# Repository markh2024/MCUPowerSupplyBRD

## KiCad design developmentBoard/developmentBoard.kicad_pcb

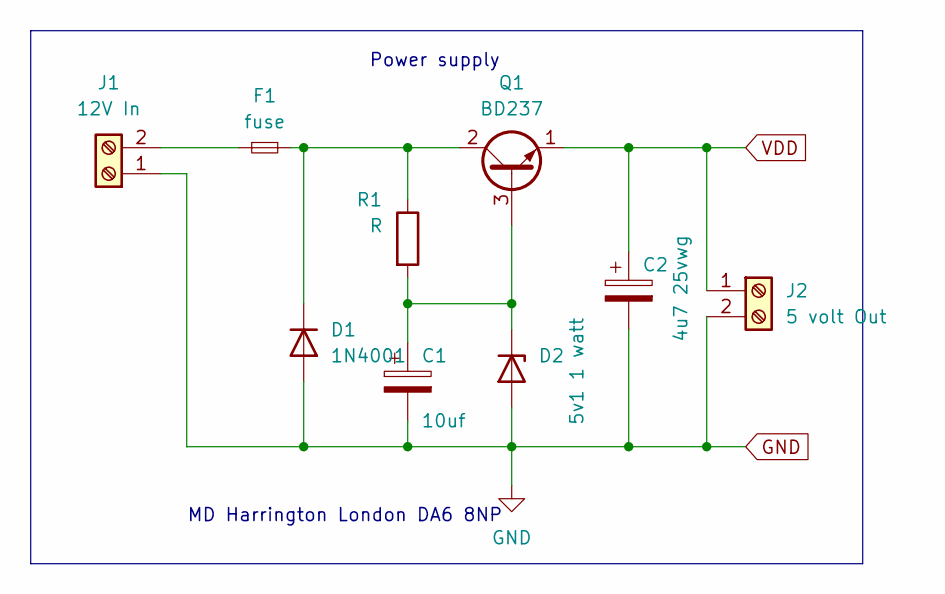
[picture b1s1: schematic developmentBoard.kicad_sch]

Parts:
C1: 10uf; CP_Radial_D4.0mm_P1.50mm
C2: 4u7 25vwg; CP_Radial_D4.0mm_P1.50mm
D1: 1N4001; D_DO-41_SOD81_P7.62mm_Horizontal
D2: 5v1 1 watt; D_A-405_P7.62mm_Horizontal
F1: fuse; Fuseholder_Clip-5x20mm_Eaton_1A5601-01_Inline_P20.80x6.76mm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
J1: 12V In; TerminalBlock_bornier-2_P5.08mm
J2: 5 volt Out; TerminalBlock_bornier-2_P5.08mm
Q1: BD237; TO-126-3_Vertical
R1: R; R_Axial_DIN0207_L6.3mm_D2.5mm_P10.16mm_Horizontal

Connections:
GND: C1.2, C2.2, D1.2 (A), D2.2 (A), J1.1, J2.2
unnamed: C1.1, D2.1 (K), Q1.3 (B), R1.2
unnamed: D1.1 (K), F1.2, Q1.2 (C), R1.1
unnamed: F1.1, J1.2
VDD: C2.1, J2.1, Q1.1 (E)

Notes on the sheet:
MD Harrington London DA6 8NP
Power supply

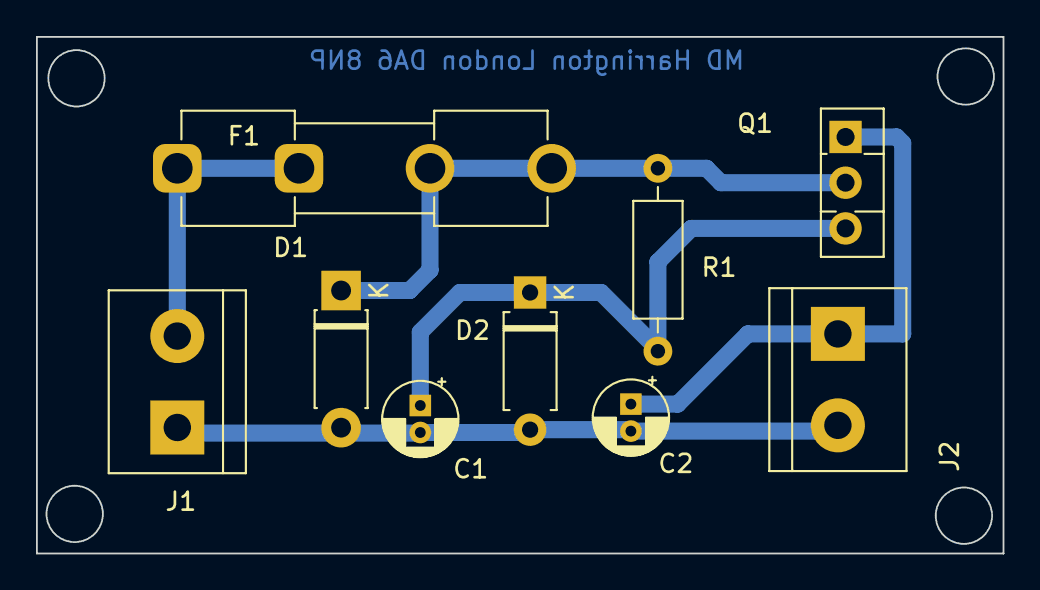
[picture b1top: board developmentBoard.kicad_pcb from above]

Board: 2 copper layers, 53.7 x 28.7 mm, 9 parts (0 on the bottom side), 5 nets.
